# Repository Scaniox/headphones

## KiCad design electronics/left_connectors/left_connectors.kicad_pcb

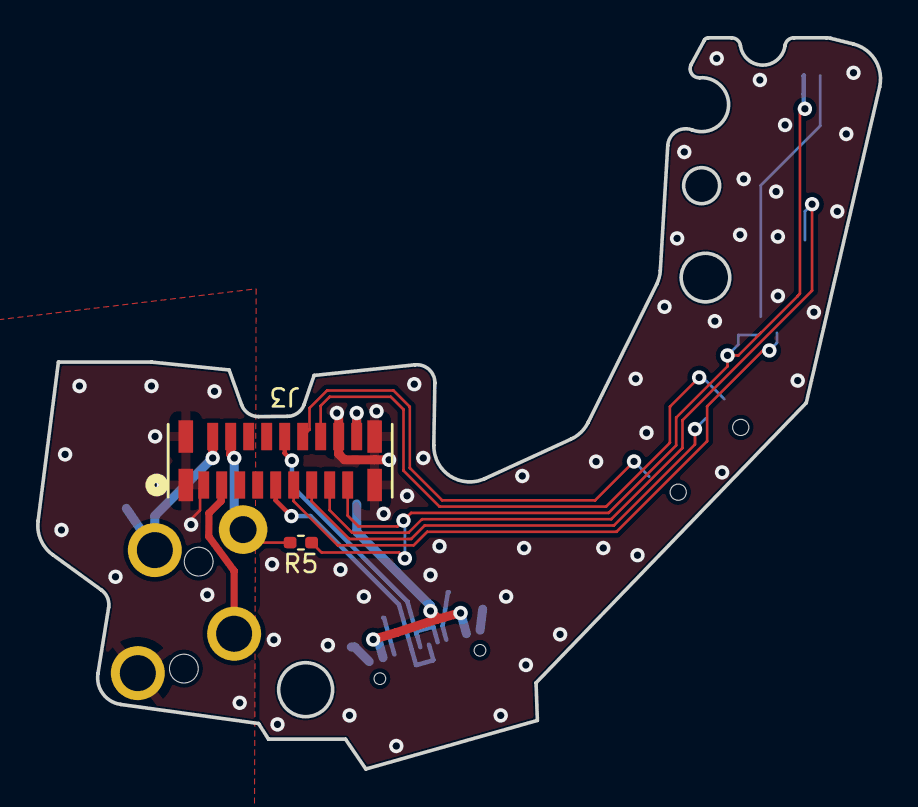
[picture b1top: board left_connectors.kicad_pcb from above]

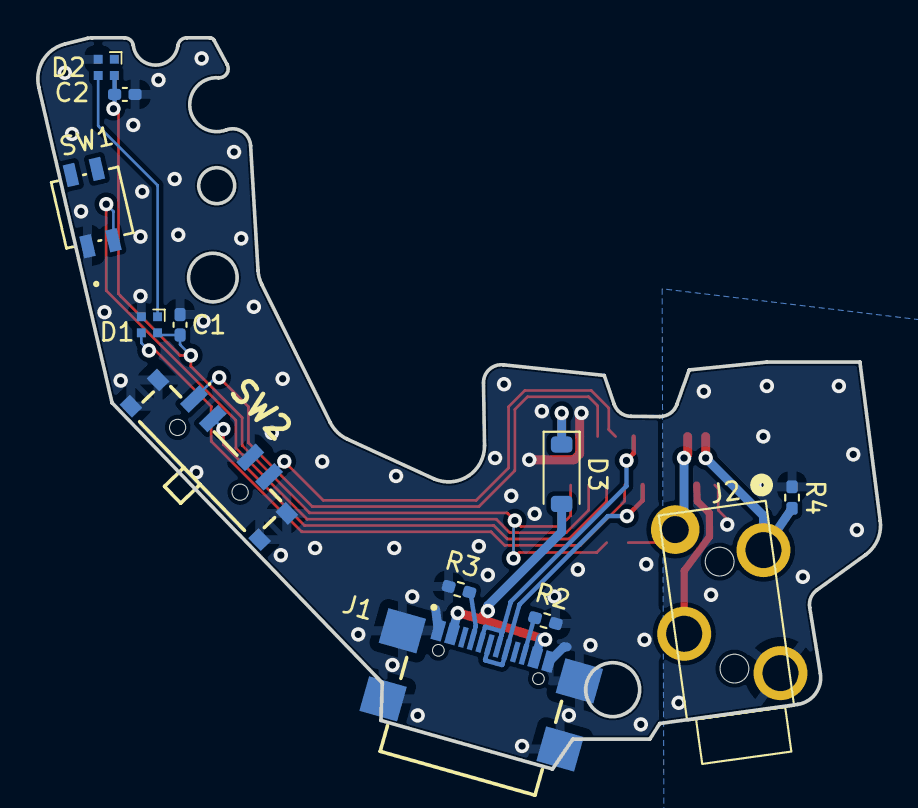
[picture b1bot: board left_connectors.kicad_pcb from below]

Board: 2 copper layers, 46.8 x 40.6 mm, 14 parts (12 on the bottom side), 18 nets.

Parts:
C1, C2: 1uF; C_0402_1005Metric_Pad0.74x0.62mm_HandSolder
D1: power_led; LED_SK6812_EC15_1.5x1.5mm
D2: ANC_led; LED_SK6812_EC15_1.5x1.5mm
D3: MBR120; D_SOD-123
J1: USB_C_Receptacle_USB2.0; GCT_USB4110-GF-A_REVB
J2: Audio In; 4832.2330
J3: Main board; CON18_1X18_DUTB_HRS_HIR
R2, R3: 5.1K; R_0402_1005Metric_Pad0.72x0.64mm_HandSolder
R4: 10k; R_0402_1005Metric_Pad0.72x0.64mm_HandSolder
R5: 50k; R_0402_1005Metric_Pad0.72x0.64mm_HandSolder
SW1: Power; EVQ_P7_PAN
SW2: ANC_control; CUS13B

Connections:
+3V3: C1.1, C2.1, D1.3 (VDD), D2.3 (VDD), J3.17, R5.1
/ANC_OFF: J3.13, SW2.2
/ANC_ON: J3.14, SW2.1
/ANC_PBO: J3.12, SW2.4
/LEDs_data_in: D1.2 (DIN), J3.11
/PWR_SW: J3.15, SW1.2 (B)
/USB_D+: J1.A6 (D+), J1.B6 (D+), J3.9
/USB_D-: J1.A7 (D-), J1.B7 (D-), J3.10
/audio_in_L: J2.T, J3.2, R4.1
/audio_in_R: J2.R, J3.3
/audio_in_detect: J2.TN, J3.4, R5.2
GND: C1.2, C2.2, D1.1 (VSS), D2.1 (VSS), J1.A1 (GND), J1.B1 (GND), J1.S1 (SHIELD), J3.16, J3.19, J3.21, R2.2, R3.2, SW1.1 (A), SW2.3, SW2.MP1, SW2.MP2, SW2.MP3, SW2.MP4
GNDA: J2.S, J3.1, J3.20, J3.22, R4.2
unnamed: D1.4 (DOUT), D2.2 (DIN)
unnamed: D3.2 (A), J1.A4 (VBUS), J1.B4 (VBUS)
unnamed: J1.A5 (CC1), R3.1
unnamed: J1.B5 (CC2), R2.1
VBUS: D3.1 (C), J3.18

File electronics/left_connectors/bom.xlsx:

Id | Designator | Footprint | Quantity | Designation | Supplier and ref | Column1 | _1
1 | J3 | CON18_1X18_DUTB_HRS_HIR | 1 | Main board | https://www.digikey.co.uk/en/products/detail/hirose-electric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 | 1.3
2 | R5 | R_0402_1005Metric_Pad0.72x0.64mm_HandSolder | 1 | 47k | https://www.digikey.co.uk/en/products/detail/yageo/RC0402FR-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 | 5.8999999999999999E-3
3 | D1, D2 | LED_SK6812_EC15_1.5x1.5mm | 2 | ANC_led, power_led | have
4 | SW2 | CUS13B | 1 | ANC_control | https://www.digikey.co.uk/en/products/detail/nidec-component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 | 0.73
5 | R2,R3 | R_0402_1005Metric_Pad0.72x0.64mm_HandSolder | 2 | 5.1K | have
6 | R4 | R_0402_1005Metric_Pad0.72x0.64mm_HandSolder | 1 | 10k | have
8 | D3 | D_SOD-123 | 1 | MBR120 | https://www.digikey.co.uk/en/products/detail/panjit-internat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
9 | C1,C2 | C_0402_1005Metric_Pad0.74x0.62mm_HandSolder | 2 | 1uF | have
10 | J1 | GCT_USB4110-GF-A_REVB | 1 | USB_C_Receptacle_USB2.0 | have
11 | J2 | 4832.2330000000002 | 1 | Audio In | https://www.digikey.co.uk/en/products/detail/schurter-inc/48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 | 1.18
12 | SW1 | EVQ_P7_PAN | 1 | Power | https://www.digikey.co.uk/en/products/detail/panasonic-elect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

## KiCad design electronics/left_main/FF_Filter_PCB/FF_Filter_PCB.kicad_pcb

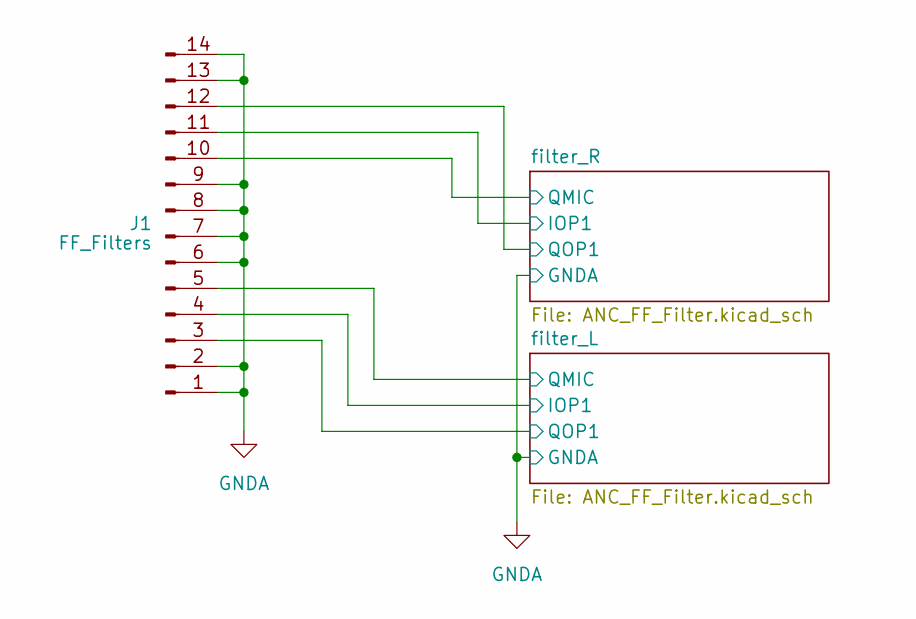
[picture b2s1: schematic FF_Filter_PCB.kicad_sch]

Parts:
J1: FF_Filters; Hirose_DF12_DF12C3.0-14DS-0.5V_2x07_P0.50mm_Vertical

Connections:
/filter_L/IOP1: J1.4; also elsewhere on the board
/filter_L/QMIC: J1.5; also elsewhere on the board
/filter_L/QOP1: J1.3; also elsewhere on the board
/filter_R/IOP1: J1.11; also elsewhere on the board
/filter_R/QMIC: J1.10; also elsewhere on the board
/filter_R/QOP1: J1.12; also elsewhere on the board
GNDA: J1.1, J1.2, J1.6, J1.7, J1.8, J1.9, J1.13, J1.14; also elsewhere on the board

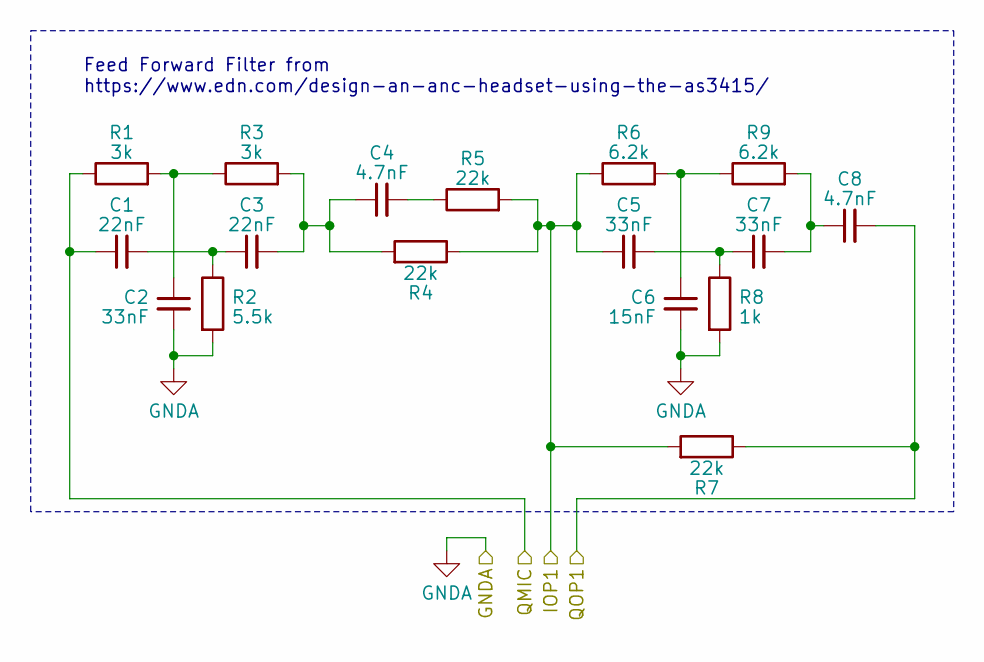
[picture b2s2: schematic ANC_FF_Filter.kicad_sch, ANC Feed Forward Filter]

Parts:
C1, C3: 22nF; C_0402_1005Metric_Pad0.74x0.62mm_HandSolder
C2, C5, C7: 33nF; C_0402_1005Metric_Pad0.74x0.62mm_HandSolder
C4, C8: 4.7nF; C_0402_1005Metric_Pad0.74x0.62mm_HandSolder
C6: 15nF; C_0402_1005Metric_Pad0.74x0.62mm_HandSolder
R1, R3: 3k; R_0402_1005Metric_Pad0.72x0.64mm_HandSolder
R2: 5.5k; R_0402_1005Metric_Pad0.72x0.64mm_HandSolder
R4, R5, R7: 22k; R_0402_1005Metric_Pad0.72x0.64mm_HandSolder
R6, R9: 6.2k; R_0402_1005Metric_Pad0.72x0.64mm_HandSolder
R8: 1k; R_0402_1005Metric_Pad0.72x0.64mm_HandSolder

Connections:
/filter_R/IOP1: C5.1, R4.1, R5.2, R6.1, R7.2; also elsewhere on the board
/filter_R/QMIC: C1.1, R1.1; also elsewhere on the board
/filter_R/QOP1: C8.2, R7.1; also elsewhere on the board
GNDA: C2.2, C6.2, R2.2, R8.2; also elsewhere on the board
unnamed: C1.2, C3.1, R2.1
unnamed: C2.1, R1.2, R3.1
unnamed: C3.2, C4.1, R3.2, R4.2
unnamed: C4.2, R5.1
unnamed: C5.2, C7.1, R8.1
unnamed: C6.1, R6.2, R9.1
unnamed: C7.2, C8.1, R9.2

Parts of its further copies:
C9, C11: 22nF; C_0402_1005Metric_Pad0.74x0.62mm_HandSolder
C10, C13, C15: 33nF; C_0402_1005Metric_Pad0.74x0.62mm_HandSolder
C12, C16: 4.7nF; C_0402_1005Metric_Pad0.74x0.62mm_HandSolder
C14: 15nF; C_0402_1005Metric_Pad0.74x0.62mm_HandSolder
R10, R12: 3k; R_0402_1005Metric_Pad0.72x0.64mm_HandSolder
R11: 5.5k; R_0402_1005Metric_Pad0.72x0.64mm_HandSolder
R16: 22k; R_0402_1005Metric_Pad0.72x0.64mm_HandSolder
R18: 6.2k; R_0402_1005Metric_Pad0.72x0.64mm_HandSolder

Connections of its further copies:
/filter_L/IOP1: C13.1, R16.2; also elsewhere on the board
/filter_L/QMIC: C9.1, R10.1; also elsewhere on the board
/filter_L/QOP1: C16.2, R16.1; also elsewhere on the board
GNDA: C10.2, C14.2, R11.2; also elsewhere on the board
unnamed: C10.1, R10.2, R12.1
unnamed: C9.2, C11.1, R11.1
unnamed 16: C11.2, C12.1, R12.2; also elsewhere on the board
unnamed 17: C12.2; also elsewhere on the board
unnamed 18: C13.2, C15.1; also elsewhere on the board
unnamed 19: C14.1, R18.1; also elsewhere on the board
unnamed: C15.2, C16.1, R18.2

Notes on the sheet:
Feed Forward Filter from https://www.edn.com/design-an-anc-headset-using-the-as3415/

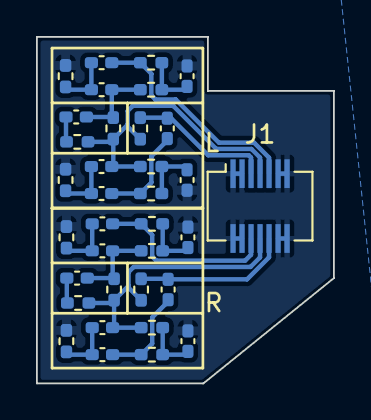
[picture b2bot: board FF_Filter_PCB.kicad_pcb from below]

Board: 4 copper layers, 16.5 x 19.2 mm, 35 parts (35 on the bottom side), 21 nets.

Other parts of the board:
R13, R14: 22k; R_0402_1005Metric_Pad0.72x0.64mm_HandSolder
R15: 6.2k; R_0402_1005Metric_Pad0.72x0.64mm_HandSolder
R17: 1k; R_0402_1005Metric_Pad0.72x0.64mm_HandSolder

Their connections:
/filter_L/IOP1: R13.1, R14.2, R15.1; also elsewhere on the board
GNDA: R17.2; also elsewhere on the board
unnamed 16: R13.2; also elsewhere on the board
unnamed 17: R14.1; also elsewhere on the board
unnamed 18: R17.1; also elsewhere on the board
unnamed 19: R15.2; also elsewhere on the board

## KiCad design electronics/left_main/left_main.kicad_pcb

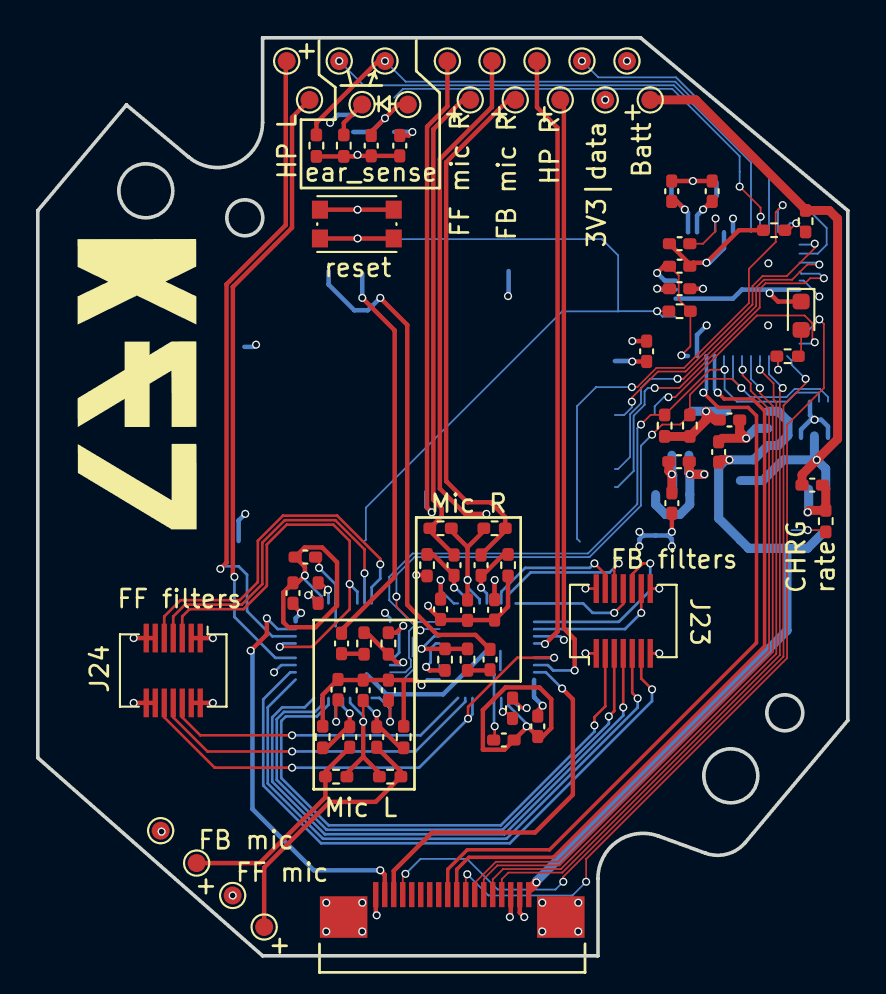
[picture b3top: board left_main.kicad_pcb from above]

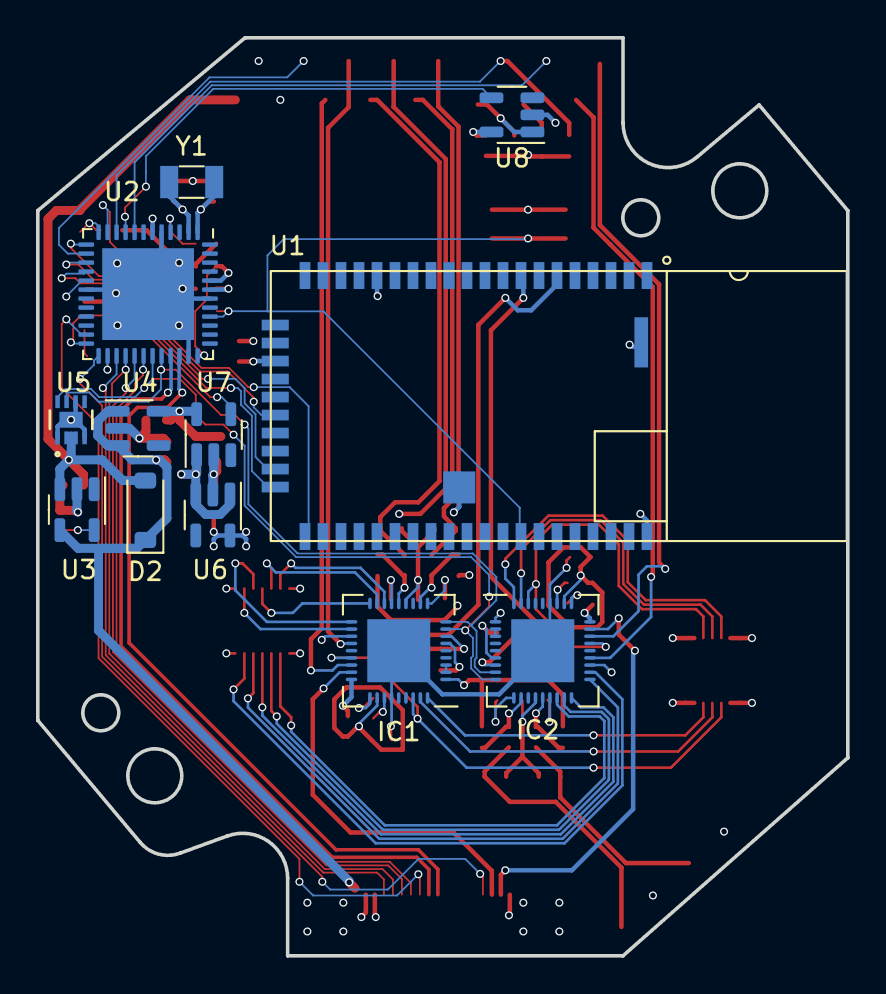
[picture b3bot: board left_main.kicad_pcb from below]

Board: 4 copper layers, 45.0 x 51.0 mm, 89 parts (12 on the bottom side), 87 nets.

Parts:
C1, C6, C7, C8, C9, C10, C11, C12, C13, C15, C16, C47, C48, C49, C50, C52, C56, C58, C79: 10uF; C_0402_1005Metric_Pad0.74x0.62mm_HandSolder
C2, C3, C17, C54, C75, C76, C77: 1uF; C_0402_1005Metric_Pad0.74x0.62mm_HandSolder
C4, C5: 22pF; C_0402_1005Metric_Pad0.74x0.62mm_HandSolder
C14, C43: 470nF; C_0402_1005Metric_Pad0.74x0.62mm_HandSolder
C78: 0.1uF; C_0402_1005Metric_Pad0.74x0.62mm_HandSolder
D1: RED; LED_0603_1608Metric
D2: MBR120; D_SOD-123
IC1, IC2: AS3435-EQFM; QFN-36_EP_5.9x5.9_Pitch0.4mm
J1: connectors_board; CON18_1X18_DR_SFV_GLE
J3: FF_MIC_L_+; TestPoint_Pad_D1.0mm
J4: FF_MIC_L_-; TestPoint_Pad_D1.0mm
J5: FB_MIC_L_+; TestPoint_Pad_D1.0mm
J6: FB_MIC_L_-; TestPoint_Pad_D1.0mm
J7: HP_L_+; TestPoint_Pad_D1.0mm
J8: HP_L_-; TestPoint_Pad_D1.0mm
J9, J10, J11, J12, J13, J14, J15, J16, J17, J18: right_side; TestPoint_Pad_D1.0mm
J19, J20, J21, J22: ear_sensor; TestPoint_Pad_D1.0mm
J23: FB_Filters; Hirose_DF12_DF12E3.0-14DP-0.5V_2x07_P0.50mm_Vertical
J24: FF_Filters; Hirose_DF12_DF12E3.0-14DP-0.5V_2x07_P0.50mm_Vertical
R1, R8, R9, R10, R11, R43, R47, R49, R53: 2.2k; R_0402_1005Metric_Pad0.72x0.64mm_HandSolder
R2, R3, R5: 100k; R_0402_1005Metric_Pad0.72x0.64mm_HandSolder
R4: 6.8K; R_0402_1005Metric_Pad0.72x0.64mm_HandSolder
R6, R7, R42, R44, R74, R75: 10k; R_0402_1005Metric_Pad0.72x0.64mm_HandSolder
R72: 200; R_0402_1005Metric_Pad0.72x0.64mm_HandSolder
R73: 68k; R_0402_1005Metric_Pad0.72x0.64mm_HandSolder
SW2: reset_button; SW_Push_1P1T_NO_CK_KMR2
U1: BM83
U2: ATSAMD21G18_QFN; TQFN-48-1EP_7x7mm_P0.5mm_EP5.1x5.1mm
U3: MCP73831T-2ACI/OT; SOT-23-5
U4: SPX3819-3.3; SOT-23-5
U5: MAX17048G+T10; 21-0168E_T822-3_MXM
U6: AP2127K-1.8; SOT-23-5
U7, U8: AP22814AW5; SOT-23-5
Y1: 32.768KHz; Crystal_SMD_3215-2Pin_3.2x1.5mm

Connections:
+1V8: C15.1, C58.1, C76.1, IC1.27 (VBAT), IC2.27 (VBAT), U6.5 (VOUT)
+3V3: C1.1, C75.1, C79.1, J1.17, J17.1, U1.23 (BAT_IN), U6.1 (VIN), U6.3 (EN), U7.1 (OUT), U8.5 (IN)
+BATT: C6.1, D2.2 (A), J16.1, R2.1, U3.3 (VBAT), U5.2 (CELL), U5.3 (VDD)
/3V3_EN: U2.24 (PA15/I15/SERCOM3+4.3), U7.4 (EN)
/A2: J22.1, U2.8 (PB09/I9/AIN3/SERCOM4.1)
/A3: U2.9 (PA04/EINT4/VREFB/AIN4/SERCOM0.0), U8.4 (EN)
/A4: J21.1, R73.1, U2.10 (PA05/EINT5/AIN5/SERCOM0.1)
/ANC_OFF: J1.13, U2.29 (PA20/I4/SERCOM3+5.2/I2SSC)
/ANC_ON: J1.14, U2.28 (PA19/I3/SERCOM1+3.3/I2SD0)
/ANC_PBO: J1.12, U2.30 (PA21/I5/SERCOM3+5.3/I2SFS0)
/AOHPL: C43.1, U1.8 (AOHPL)
/AOHPR: C14.1, U1.6 (AOHPR)
/AREF: C77.1, U2.4 (PA03/EINT3/VREFA/AIN1)
/BAT_V_SENSE: R2.2, R3.1, U2.12 (PA07/I7/AIN7/SERCOM0.3/I2SD0)
/BM83_PROG_EN: U1.31 (P3_4/UART_RTS), U2.11 (PA06/EINT6/AIN6/SERCOM0.2)
/BM83_UART_RX: U1.29 (P8_6/UART_RXD), U2.15 (PA10/I10/AIN18/SERCOM0+2.2/I2SCK)
/BM83_UART_TX: U1.30 (P8_5/UART_TXD), U2.16 (PA11/I11/AIN19/SERCOM0+2.3/I2SF0)
/D2: J1.11, U2.23 (PA14/I14/SERCOM2+4.2)
/D3: J15.1, U2.14 (PA09/I2C/I9/AIN17/SERCOM0+2.1/I2SMC)
/D4: U1.26 (PWR(MFB)), U2.13 (PA08/I2C/AIN16/SERCOM0+2.0/I2SD1)
/D10: J1.15, U2.27 (PA18/I2/SERCOM1+3.2)
/D11: J1.4, U2.25 (PA16/I2C/I0/SERCOM1+3.0)
/D13: R1.1, U2.26 (PA17/I2C/I1/SERCOM1+3.1)
/FB_IOP1_L: IC2.17 (IOP1R), J23.3
/FB_IOP1_R: IC1.17 (IOP1R), J23.10
/FB_IOP2_L: IC2.19 (IOP2R), J23.5
/FB_IOP2_R: IC1.19 (IOP2R), J23.12
/FB_QMIC_L: IC2.16 (QMICR), J23.2
/FB_QMIC_R: IC1.16 (QMICR), J23.9
/FB_QOP1_L: IC2.18 (QOP1R), J23.4
/FB_QOP1_R: IC1.18 (QOP1R), J23.11
/FB_QOP2_L: IC2.20 (QOP2R), J23.6
/FB_QOP2_R: IC1.20 (QOP2R), J23.13
/FB_mic_L_+: C56.1, J5.1, R49.2
/FB_mic_R_+: C10.1, J11.1, R9.2
/FF_IOP1_L: IC2.35 (IOP1L), J24.4
/FF_IOP1_R: IC1.35 (IOP1L), J24.11
/FF_QMIC_L: IC2.36 (QMICL), J24.5
/FF_QMIC_R: IC1.36 (QMICL), J24.10
/FF_QOP1_L: IC2.24 (MIXR), IC2.34 (QOP1L), J24.3
/FF_QOP1_R: IC1.24 (MIXR), IC1.34 (QOP1L), J24.12
/FF_mic_L_+: C48.2, J3.1, R47.1
/FF_mic_R_+: C9.2, J9.1, R8.1
/HP_L_+: IC2.25 (HPR), J7.1
/HP_L_-: IC2.22 (HPL), J8.1
/HP_R_+: IC1.25 (HPR), J13.1
/HP_R_-: IC1.22 (HPL), J14.1
/HP_driver_L/vneg: C16.1, C47.1, IC1.31 (VNEG), IC1.37 (EP), IC2.31 (VNEG), IC2.37 (EP)
/I2C_SCL: IC1.9 (MODE/CSCL), IC2.8 (ANC/CSDA), R74.2, U2.32 (PA23/I2C/I7/SERCOM3+5.1/SOF), U5.7 (SCL)
/I2C_SDA: IC1.8 (ANC/CSDA), IC2.9 (MODE/CSCL), R75.2, U2.31 (PA22/I2C/I6/SERCOM3+5.0), U5.8 (SDA)
/USB_D+: J1.9, U2.34 (PA25/I13/SERCOM3+5.3/D+)
/USB_D-: J1.10, U2.33 (PA24/I12/SERCOM3+5.2/D-)
/audio_in_L: IC2.26 (BPR), J1.2
/audio_in_R: IC1.26 (BPR), J1.3
/~RESET: R5.2, SW2.1 (A), U1.43 (RST_N), U2.40 (/RESET)
GND: C1.2, C2.2, C3.2, C4.1, C5.1, C6.2, C7.2, C8.2, C11.2, C12.1, C13.2, C15.2, C16.2, C47.2, C49.1, C50.2, C52.2, C58.2, C75.2, C76.2, C77.2, C78.2, C79.2, D1.1 (C), IC1.1 (AGND), IC1.21 (BPL), IC1.29 (GND), IC2.1 (AGND), IC2.21 (BPL), IC2.29 (GND), J1.1, J1.16, J1.19, J1.20, J4.1, J6.1, J10.1, J12.1, J18.1, J23.1, J23.7, J23.8, J23.14, J24.1, J24.2, J24.6, J24.7, J24.8, J24.9, J24.13, J24.14, R3.2, R4.2, R10.2, R11.2, R43.2, R53.2, R72.2, R73.2, SW2.2 (B), U1.16 (GND), U1.50 (GND), U2.5 (GNDA), U2.18 (GND), U2.35 (GND), U2.42 (GND), U2.49 (GND), U3.2 (VSS), U4.2 (GND), U5.1 (CTG), U5.4 (GND), U5.6 (QSTRT), U5.9 (EPAD), U6.2 (GND), U7.2 (GND), U8.2 (GND)
unnamed: C14.2, R7.1
unnamed: C43.2, R42.1
unnamed: D1.2 (A), R1.2
unnamed: C17.1, IC1.30 (CPN)
unnamed: C17.2, IC1.28 (CPP)
unnamed: IC1.2 (QLINL), IC1.3 (LINL)
unnamed: IC1.6 (LINR), R6.2
unnamed: C12.2, IC1.10 (MICACL)
unnamed: C13.1, IC1.15 (MICACR)
unnamed: C9.1, IC1.11 (MICL), R11.1
unnamed: C10.2, IC1.14 (MICR), R10.1
unnamed: C11.1, IC1.13 (MICS), R8.2, R9.1
unnamed: IC1.7 (QLINR), R6.1, R7.2
unnamed: C54.1, IC2.30 (CPN)
unnamed: C54.2, IC2.28 (CPP)
unnamed: IC2.2 (QLINL), IC2.3 (LINL)
unnamed: IC2.6 (LINR), R44.2
unnamed: C49.2, IC2.10 (MICACL)
unnamed: C52.1, IC2.15 (MICACR)
unnamed: C48.1, IC2.11 (MICL), R43.1
unnamed: C56.2, IC2.14 (MICR), R53.1
unnamed: C50.1, IC2.13 (MICS), R47.2, R49.1
unnamed: IC2.7 (QLINR), R42.2, R44.1
unnamed: J20.1, R72.1
unnamed: C4.2, U2.1 (PA00/EINT0/SERCOM1.0), Y1.1
unnamed: C5.2, U2.2 (PA01/EINT1/SERCOM1.1), Y1.2
unnamed: C3.1, U2.43 (VDDCORE)
unnamed: R4.1, U3.5 (PROG)
unnamed: C78.1, J19.1, U8.1 (OUT)
VBUS: C7.1, D2.1 (C), J1.18, U3.4 (VDD), U4.1 (IN), U4.3 (EN)
VDD: C2.1, C8.1, R5.1, R74.1, R75.1, U2.6 (VDDA), U2.17 (VDDIO), U2.36 (VDDIO), U2.44 (VDDIN), U4.5 (OUT), U7.5 (IN)

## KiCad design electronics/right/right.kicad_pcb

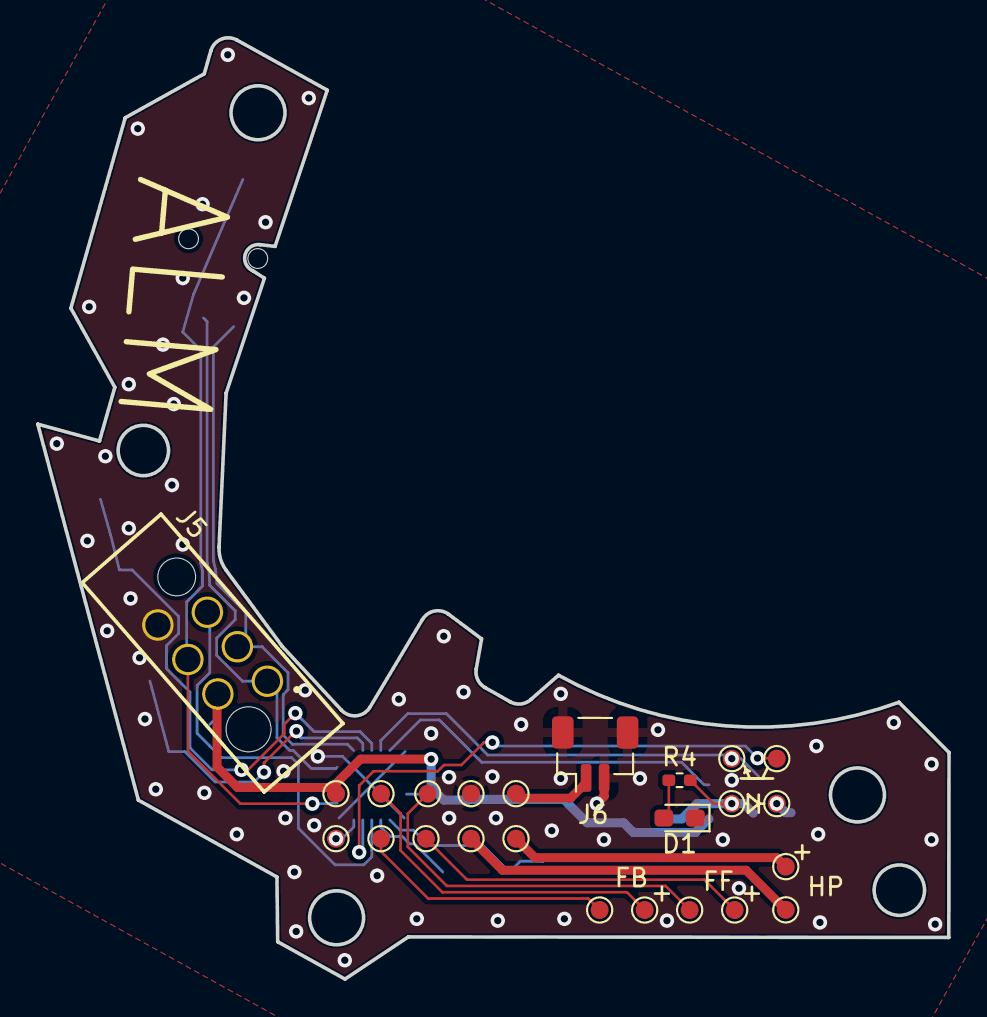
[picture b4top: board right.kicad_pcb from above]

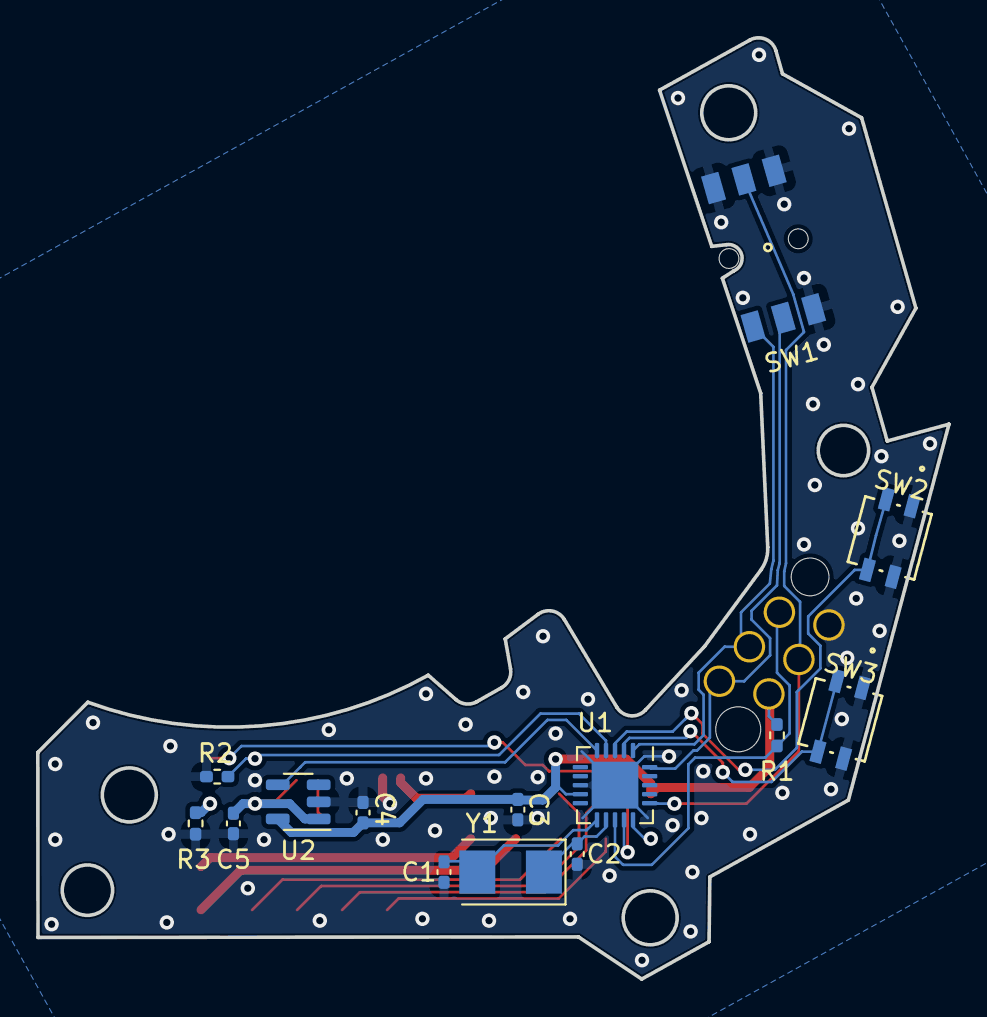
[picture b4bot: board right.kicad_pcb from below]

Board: 2 copper layers, 50.6 x 52.3 mm, 38 parts (14 on the bottom side), 24 nets.

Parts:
C1, C2: 18pF; C_0402_1005Metric_Pad0.74x0.62mm_HandSolder
C3: 10uf; C_0402_1005Metric_Pad0.74x0.62mm_HandSolder
C4: 10uF; C_0402_1005Metric_Pad0.74x0.62mm_HandSolder
C5: 0.1uF; C_0402_1005Metric_Pad0.74x0.62mm_HandSolder
D1: LED; LED_0603_1608Metric_Pad1.05x0.95mm_HandSolder
J5: programming; 490107670612
J6: Batt; JST_SH_BM02B-SRSS-TB_1x02-1MP_P1.00mm_Vertical
R1: 10k; R_0402_1005Metric_Pad0.72x0.64mm_HandSolder
R2: 68k; R_0402_1005Metric_Pad0.72x0.64mm_HandSolder
R3: 200; R_0402_1005Metric_Pad0.72x0.64mm_HandSolder
R4: 220; R_0402_1005Metric_Pad0.72x0.64mm_HandSolder
SW1: jog stick; JLS1300-08-1F
SW2: Volume up; EVQ_P7_PAN
SW3: Volume down; EVQ_P7_PAN
TP1, TP2, TP3, TP4, TP5, TP6, TP7, TP8, TP9, TP10, TP11, TP12, TP13, TP14, TP15, TP16, TP17, TP18, TP19, TP20: TestPoint; TestPoint_Pad_D1.0mm
U1: ATtiny441-M; QFN-20-1EP_4x4mm_P0.5mm_EP2.6x2.6mm
U2: AP22814AW5; SOT-23-5
Y1: 8Mhz; Crystal_SMD_5032-2Pin_5.0x3.2mm

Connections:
+3V3: C3.1, C4.1, J5.2, R1.1, TP8.1, U1.9 (VCC), U2.5 (IN)
+BATT: J6.1, TP9.1
/FB_mic_R_+: TP3.1, TP14.1
/FB_mic_R_-: TP4.1, TP15.1
/FF_mic_R_+: TP1.1, TP16.1
/FF_mic_R_-: TP2.1, TP13.1
/HP_R_+: TP5.1, TP10.1
/HP_R_-: TP6.1, TP11.1
/MISO: J5.1, SW1.5 (CW), U1.20 (PA5)
/MOSI: J5.4, SW1.2 (CCW), U1.16 (PA6)
/SCK: J5.3, SW1.6 (PUSH), U1.1 (PA4)
/opto_LDR: TP20.1, U1.14 (PB2)
/opto_en: U1.5 (AREF/PA0), U2.4 (EN)
/opto_out: R2.1, TP19.1, U1.4 (PA1)
/right_side_data: TP12.1, U1.15 (PA7)
/vol_down: SW3.2, U1.2 (PA3)
/vol_up: SW2.2, U1.3 (PA2)
/~reset: J5.5, R1.2, U1.13 (~RESET/PB3)
GND: C1.2, C2.2, C3.2, C4.2, C5.2, D1.1 (K), J5.6, J6.2, J6.MP, R2.2, R3.2, SW1.1 (GND), SW1.3 (GND), SW1.4 (GND), SW2.1, SW3.1, TP7.1, U1.8 (GND), U1.21 (GND), U2.2 (GND)
unnamed: D1.2 (A), R4.2
unnamed: R3.1, TP18.1
unnamed: C1.1, U1.11 (XTAL1/PB0), Y1.2
unnamed: C2.1, U1.12 (XTAL2/PB1), Y1.1
unnamed: C5.1, R4.1, TP17.1, U2.1 (OUT)

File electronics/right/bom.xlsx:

Id | Designator | Footprint | Quantity | Designation | Supplier and ref | Column1 | _1
1 | SW1 | JLS1300-08-1F | 1 | jog stick | have
2 | D1 | LED_0603_1608Metric_Pad1.05x0.95mm_HandSolder | 1 | LED | have
3 | R4 | R_0402_1005Metric_Pad0.72x0.64mm_HandSolder | 1 | 220
4 | J5 | 490107670612 | 1 | programming
5 | Y1 | Crystal_SMD_5032-2Pin_5.0x3.2mm | 1 | 8Mhz
6 | C4 | C_0402_1005Metric_Pad0.74x0.62mm_HandSolder | 1 | 10uF
7 | SW3 | EVQ_P7_PAN | 1 | Volume down | https://www.digikey.co.uk/en/products/detail/panasonic-elect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
8 | SW2 | EVQ_P7_PAN | 1 | Volume up | https://www.digikey.co.uk/en/products/detail/panasonic-elect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
10 | C5 | C_0402_1005Metric_Pad0.74x0.62mm_HandSolder | 1 | 0.1uF
11 | U2 | SOT-23-5 | 1 | AP22814AW5 | https://www.digikey.co.uk/en/products/detail/diodes-incorpor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
12 | C3 | C_0402_1005Metric_Pad0.74x0.62mm_HandSolder | 1 | 10uf
13 | U1 | QFN-20-1EP_4x4mm_P0.5mm_EP2.6x2.6mm | 1 | ATtiny441-M | https://www.digikey.co.uk/en/products/detail/microchip-techn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
14 | R2 | R_0402_1005Metric_Pad0.72x0.64mm_HandSolder | 1 | 68k
15 | R1 | R_0402_1005Metric_Pad0.72x0.64mm_HandSolder | 1 | 10k
16 | J6 | JST_SH_BM02B-SRSS-TB_1x02-1MP_P1.00mm_Vertical | 1 | Batt | https://www.digikey.co.uk/en/products/detail/jst-sales-ameri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
17 | C1,C2 | C_0402_1005Metric_Pad0.74x0.62mm_HandSolder | 2 | 18pF
18 | R3 | R_0402_1005Metric_Pad0.72x0.64mm_HandSolder | 1 | 200

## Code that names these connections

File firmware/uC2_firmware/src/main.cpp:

/*******************************************************************************
 *         File: headphones\firmware\uC2_firmware\src\main.cpp
 *       Author: Alexander Mills (Scaniox#7130)
 *      License: 
 *         Date: 
 *  Description: 
 ******************************************************************************/

/* chip datasheet:
https://ww1.microchip.com/downloads/en/DeviceDoc/Atmel-8495-8-bit-AVR-Microcontrollers-ATtiny441-ATtiny841_Datasheet.pdf
*/

/* pinout:
 * PA0 - opto led enable
 * PA1 - opto output
 * PA2 - vol_up
 * PA3 - vol_down
 * PA4 - pause
 * PA5 - back
 * PA6 - Forward
 * PA7 - right_side_data
 * 
 * PB2 - opto_LDR enable
 * PB3 - reset
 */

/* fuse setup
 * keep defaults
 *
 */

#include <Arduino.h>
#include <avr/sleep.h>
#include <avr/interrupt.h>
#include <avr/wdt.h>

enum {
    VOL_UP,
    VOL_DOWN,
    PAUSE,
    BACK,
    FWRD,
};

#define DEBOUNCE_WAIT_TIME 50
#define DEBOUNCE_HOLDOFF_TIME 100

#define VOL_HOLD_START_TIME 500
#define VOL_HOLD_REPEAT_TIME 300

#define P_VOL_UP    PIN_PA2
#define P_VOL_DOWN  PIN_PA3
#define P_PAUSE     PIN_PA4
#define P_BACK      PIN_PA5
#define P_FWRD      PIN_PA6

#define P_OPTO_LED_EN   PIN_PA0
#define P_OPTO_LDR_EN   PIN_PB2
#define P_OPTO_OUT      PIN_PA1
#define P_DATA_OUT      PIN_PA7 // USART0 TX alternate pin

int last_press_time = 0;

// transmit the positions of all the buttons
void send_button_states() {
    uint8_t buttons = 0x80;
    buttons |= (!digitalRead(P_VOL_UP) & 0x01) << VOL_UP;
    buttons |= (!digitalRead(P_VOL_DOWN) & 0x01) << VOL_DOWN;
    buttons |= (!digitalRead(P_PAUSE) & 0x01) << PAUSE;
    buttons |= (!digitalRead(P_BACK) & 0x01) << BACK;
    buttons |= (!digitalRead(P_FWRD) & 0x01) << FWRD;
    Serial.write(buttons);
}

void stop_repeat_timer() {
    TCCR1B &= !(_BV(CS12) | _BV(CS11) | _BV(CS10));
}

// starts repeat timer
void start_repeat_timer(uint16_t repeat_count) {
    stop_repeat_timer();
    TCNT1 = 0;
    OCR1A = repeat_count;
    TCCR1B = _BV(CS12) | _BV(CS10);
}


// pin change interrupt
ISR(PCINT0_vect) {
    for (int _=0; _< DEBOUNCE_WAIT_TIME; _++) {
        delayMicroseconds(1000u);
    }

    (void) send_button_states();
    // start timer 1
    start_repeat_timer(VOL_HOLD_START_TIME);

    // clear flag for this interrupt so it doesn't re-trigger immediately due to 
    // switch bounce
    GIFR |= _BV(PCIF0);
}

ISR(WDT_vect) { }

ISR(TIMER1_COMPA_vect) {
    stop_repeat_timer();

    if(!digitalRead(P_VOL_UP) || !digitalRead(P_VOL_DOWN)) {
        send_button_states();
        start_repeat_timer(VOL_HOLD_REPEAT_TIME);
    }
}

void setup() {
    cli();

    // set up pins
    pinMode(P_VOL_UP,   INPUT_PULLUP);
    pinMode(P_VOL_DOWN, INPUT_PULLUP);
    pinMode(P_PAUSE,    INPUT_PULLUP);
    pinMode(P_BACK,     INPUT_PULLUP);
    pinMode(P_FWRD,     INPUT_PULLUP);

    pinMode(P_OPTO_LDR_EN,  OUTPUT);
    pinMode(P_OPTO_LED_EN,  OUTPUT);
    pinMode(P_OPTO_OUT,     INPUT);

    // // setup button interrupts
    GIMSK |= _BV(PCIE0);
    PCMSK0 |= _BV(PCINT2) | _BV(PCINT3) |_BV(PCINT4) | _BV(PCINT5) |
              _BV(PCINT6); 

    // set up uart
    Serial.begin(9600);
    // dissable RX
    UCSR0B &= ~_BV(RXEN0); // disable RX
    // set to alternate pin (PA7)
    REMAP |= _BV(U0MAP);

    // set up vol repeat timer (tc1a)
    TCCR1A = 0;
    TCCR1B = 0;
    TIMSK1 = _BV(OCIE1A); // enable TIMER_1_COMPA_vect interrupt


    // // set up WDT
    // WDTCSR |= 1 << WDIE; // WDT interrupt

    // // start WDT
    // wdt_enable(WDTO_120MS);

    sei();
}

void loop() {
    cli();
    // pause WDT
    // sleep_disable();
    // wdt_disable();
    
    // ear sense measurement
    digitalWrite(P_OPTO_LDR_EN, HIGH);
    uint8_t dark_ear_sense = analogRead(P_OPTO_OUT) >> 1;
    digitalWrite(P_OPTO_LED_EN, HIGH);
    delay(100);
    uint8_t bright_ear_sense = analogRead(P_OPTO_OUT) >> 1;
    digitalWrite(P_OPTO_LED_EN, LOW);
    digitalWrite(P_OPTO_LDR_EN, LOW);

    // transmit over uart
    Serial.write(dark_ear_sense);
    Serial.write(bright_ear_sense);

    // start / reset WDT
    // wdt_enable(WDTO_120MS);

    sei();

    // // go to Power down mode
    // sleep_enable();
    // set_sleep_mode(SLEEP_MODE_PWR_DOWN);
    // sleep_cpu();

    delay(500);
}

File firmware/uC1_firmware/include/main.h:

/*******************************************************************************
 *         File: headphones\firmware\uC1_firmware\include\main.h
 *       Author: Alexander Mills (Scaniox#7130)
 *      License: 
 *         Date: 16/06/23
 *  Description: uc1 firmware main header
 ******************************************************************************/

#include <Arduino.h>
#include "wiring_private.h" // pinPeripheral() function
#include <samd21\include\samd21g18a.h>
#include <AS3435.h>
#include <MAX17048.h>
#include <IS2020.h>
#include <Adafruit_NeoPixel.h>
#include "event timer.h"

// settings
#define POWER_ANIM_BLINK_TIME 200
#define PAIRING_ANIM_BLINK_TIME 300

#define IDLE_BLINK_ON_TIME 100
#define IDLE_BLINK_OFF_TIME 900

#define BATTERY_CHECK_INTERVAL 2000
#define LOW_BAT_SHUTOFF_SOC 5

// button timings
#define PAIRING_HOLD_TIME 2000
#define POWER_OFF_HOLD_TIME 500


// pin definitions
#define PIN_EAR_SENSE_L_EN      A3
#define PIN_EAR_SENSE_L_OUT     A4
#define PIN_BM83_PROG_EN        8u
#define PIN_BAT_V_SENSE         9u 

#define PIN_RIGHT_SIDE_DATA     3u
#define PIN_BM83_MFB            4u
#define PIN_BM83_UART_RX        1u
#define PIN_BM83_UART_TX        0u
#define PIN_BM83_RESET          A5

#define PIN_LEDS_DATA_IN        2u
#define PIN_3V3_EN              5u
#define PIN_AUDIO_IN_DETECT     11u
#define PIN_RED_LED             PIN_LED
#define PIN_PWR_SW              10u
#define PIN_ANC_ON              12u
#define PIN_ANC_OFF             6u
#define PIN_ANC_PBO             7u

#define PIN_CHRG_STAT           MOSI
#define PIN_BAT_ALRT            MISO

// operation modes
enum OPERATION_STATES {
    STATE_OFF,
    STATE_ON,
    STATE_PAIRING,
    STATE_BM83_PROG,
};

enum ANC_MODE {
    ANC,
    MONITOR,
    PBO,
};

// animations 
enum ANIMATIONS {
    ANIM_NONE,
    ANIM_POWER_ON,
    ANIM_POWER_OFF,
    ANIM_PAIRING,
};

// right side button mask
enum RIGHT_MASK{
    VOL_UP,
    VOL_DOWN,
    PAUSE,
    BACK,
    FWRD,
    NONE,
};


// colours
#define POWER_ON_BLUE           0x0000ffff
#define POWER_OFF_RED           0x00ff0000
#define DISCONECTED_ORANGE      0x00ff7300
#define DEVICE_ONE_GREEN        0x0000ff00
#define DEVICE_TWO_PURPLE       0x008000ff


// function declarations
/******************************************************************************/
// action functions
/******************************************************************************/
// set indicator LEDS
void set_ANC_indicator(uint32_t colour);
void set_power_indicator(uint32_t colour);

// animations
void start_animation(ANIMATIONS anim);
void update_animations();

// devices
void switch_device(uint8_t device);
bool is_connected(uint8_t device);
void start_pairing();
void stop_pairing();
void read_bm83_events();
void check_battery();

// power
void power_off();
void power_on();

// debug usb
void dissable_debug_USB();
void enable_debug_USB();
void send_full_status();
void send_bt_status();
void debug_parse(String s);
void bm83_serial_bridge();

/******************************************************************************/
// interrupts
/******************************************************************************/
// power button isrs
void power_button_down_isr();
void power_button_up_isr();
void power_button_isr();

// serial isrs

// right side 
void right_button_press_handler(char right_side_data);

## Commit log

2023-04-14 FF ANC schematic done
2023-04-22 schematic done, blocks located, uC1 + PWR routed
2023-04-22 oops forgot to save and close
2023-04-22 L filterers + drivers layout
2023-04-23 filter sims
2023-04-26 drc happy, silkscreens everywhere
2023-04-26 closing odds
2023-04-27 silkscreen fixed
2023-04-27 connectors board parts allocated
2023-05-01 pcbs done, filters need to be finalised
2023-05-21 FB,FF filter separated from main schematic
2023-05-23 ff filter pcb schematic
2023-05-23 FF filter PCB done
2023-05-30 all pcbs done and ordered
2023-05-30 started on uc2 firmware
2023-05-31 pin change interrupt
2023-06-02 AS3435 interface started
2023-06-11 arm tests v0.0
2023-06-16 not much
2023-06-16 startup code
2023-06-17 initialise devices + MAX17048 driver
2023-06-22 uC2 upload protocol to ini
2023-06-23 right pcb works
2023-06-26 power button and LEDs work
2023-06-27 led animations! yay!
2023-06-27 restructure animations + usb debug
2023-06-27 bt serial bridge updating works, working toward working BT
2023-06-28 bt works
2023-06-30 testing EQs, right side tx wierd
2023-06-30 audio changes work both ways on windows
2023-07-01 now using boost eq
2023-07-01 boost ++ eq
2023-07-01 remove unnecessary if debug statements
2023-07-01 remove needless if on DBG
2023-07-01 clean up undefined behav code
2023-07-01 add speaker mute on power down
2023-07-02 animations show connection status
2023-07-02 voice prompts not converting
2023-07-03 trying to find whining noise
2023-07-03 turning everything off didn't work
2023-07-04 the EEEE was the i2c bus!!!!!!!!
2023-07-04 mcu voice prompts don't work
2023-07-04 voice prompts from mcu don't work
2023-07-05 set overall gain gives mobile vol controls
2023-07-05 vol button hold works
2023-07-06 event timer implemented
2023-07-07 power button time triggers erroneously
2023-07-07 watchdog sleep when off
2023-07-08 fixed spontaneous timer trigger - clear interrupts
2023-07-08 pcb backups
2023-07-08 volume repeat timer
2023-07-08 remove old vol button start times
2023-07-08 anim timer
2023-07-08 dissable interrupts for some timer changes
2023-07-08 inverted idle animation logic
2023-07-08 fix break errors in update anim
2023-07-08 delay for isrs
2023-07-08 added watchdog sleep to uC2
2023-07-10 dissable low battery check for current measurement
2023-07-16 swapped from milis() to RTC
2023-07-16 added event timer debug messages
2023-07-16 standby works, but dissables usb
2023-07-18 fixed the cli() round timers locking system waiting for dropped packets
2023-07-18 reduced time ISRs are dissabled
2023-07-18 change idle anim to show dev colour first
2023-07-18 remove debug prints
2023-07-18 remove more prints
2023-07-18 dissabled power saving sleep in standby mode
2023-07-18 re enabled battery checking
2023-07-20 emulate sleep for testing
2023-07-20 less sub bass eq
2023-09-06 replace pairing from power off with full system reset - should fix randomly not correctly initing btm
2023-12-03 volume button repeat on uC2 not uC1 fix ghost hold
2024-04-12 random pcb kicad backups
2024-04-12 dumped the current full firmware, and then uploaded "connected_promts.hex" as that seemed to fix the wack eq
    also wierd that firmware old is the current one - this is a terrible use of git
